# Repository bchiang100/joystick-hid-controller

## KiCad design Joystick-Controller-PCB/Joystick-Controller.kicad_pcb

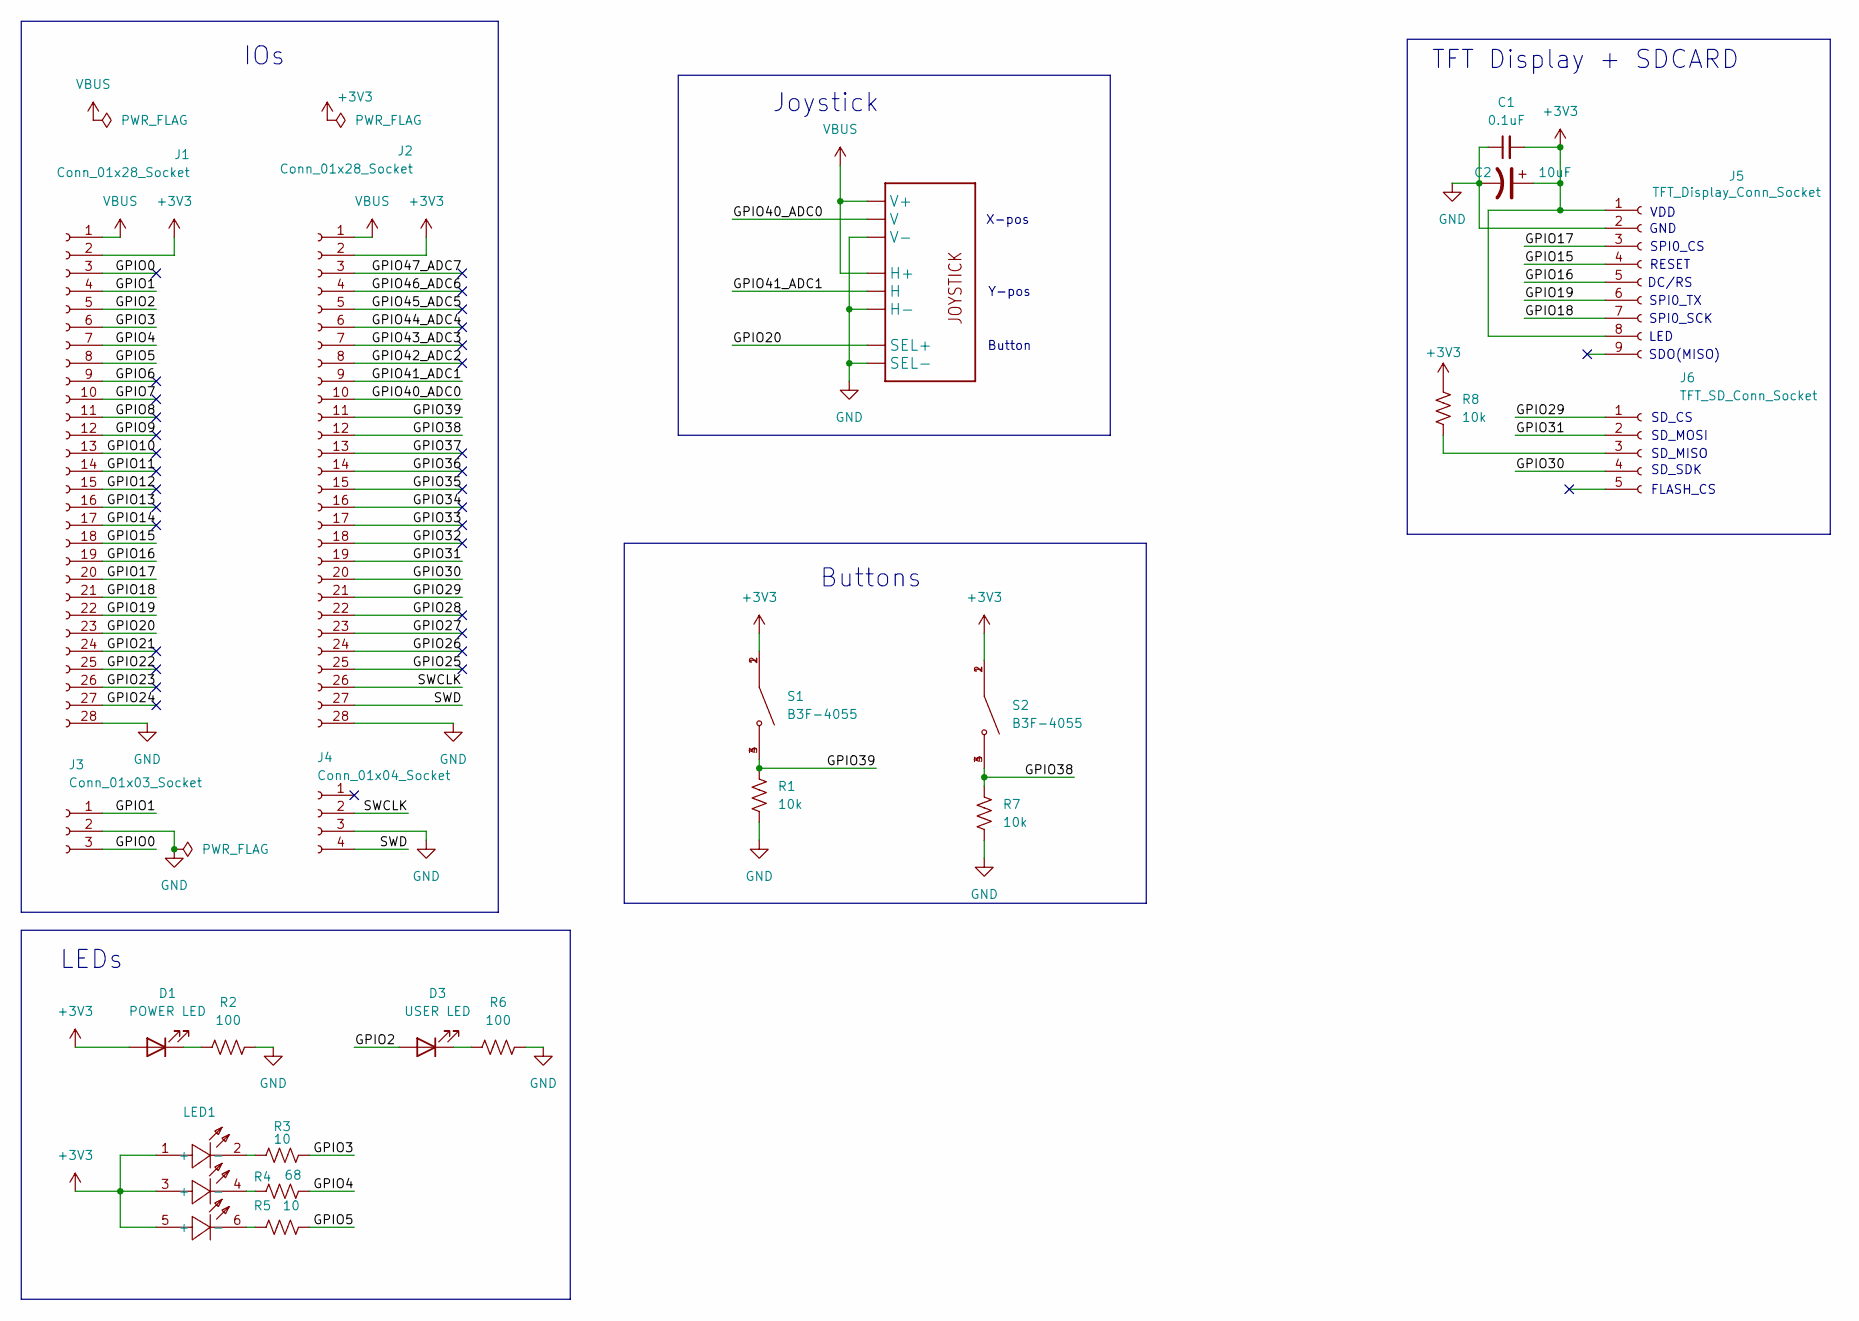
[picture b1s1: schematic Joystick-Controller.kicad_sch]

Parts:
C1: 0.1uF; CP_EIA-2012-12_Kemet-R_HandSolder
C2: 10uF; CP_EIA-2012-12_Kemet-R_HandSolder
D1: POWER LED; D_0805_2012Metric_Pad1.15x1.40mm_HandSolder
D3: USER LED; LED_0603_1608Metric_Pad1.05x0.95mm_HandSolder
J1, J2: Conn_01x28_Socket; PinSocket_1x28_P2.54mm_Vertical
J3: Conn_01x03_Socket; PinSocket_1x03_P2.54mm_Vertical
J4: Conn_01x04_Socket; PinSocket_1x04_P2.54mm_Vertical
J5: TFT_Display_Conn_Socket; PinSocket_1x09_P2.54mm_Vertical
J6: TFT_SD_Conn_Socket; PinSocket_1x05_P2.54mm_Vertical
LED1: LED-SMD_6PIN-L1.60-W1.50-BL-RD; Manufacturer Part E6C1615RGBC3UDA; LCSC Part Name RGB三色
R1, R7, R8: 10k; R_0805_2012Metric_Pad1.20x1.40mm_HandSolder
R2, R6: 100; R_0805_2012Metric_Pad1.20x1.40mm_HandSolder
R3, R5: 10; R_0805_2012Metric_Pad1.20x1.40mm_HandSolder
R4: 68; R_0805_2012Metric_Pad1.20x1.40mm_HandSolder
S1, S2: B3F-4055; SW_B3F-4055; PARTREV A070-E1-08
U1: XDCR_COM-09032

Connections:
+3V3: C1.2, C2.1, D1.2 (A), J1.2, J2.2, J5.1, J5.8, LED1.1 (+), LED1.3 (+), LED1.5 (+), R8.1, S1.1, S1.2, S2.1, S2.2
/GPIO0: J1.3, J3.3
/GPIO1: J1.4, J3.1
/GPIO2: D3.2 (A), J1.5
/GPIO3: J1.6, R3.2
/GPIO4: J1.7, R4.2
/GPIO5: J1.8, R5.2
/GPIO6: J1.9
/GPIO7: J1.10
/GPIO8: J1.11
/GPIO9: J1.12
/GPIO10: J1.13
/GPIO11: J1.14
/GPIO12: J1.15
/GPIO13: J1.16
/GPIO14: J1.17
/GPIO15: J1.18, J5.4
/GPIO16: J1.19, J5.5
/GPIO17: J1.20, J5.3
/GPIO18: J1.21, J5.7
/GPIO19: J1.22, J5.6
/GPIO20: J1.23, U1.B1A (SEL+)
/GPIO21: J1.24
/GPIO22: J1.25
/GPIO23: J1.26
/GPIO24: J1.27
/GPIO25: J2.25
/GPIO26: J2.24
/GPIO27: J2.23
/GPIO28: J2.22
/GPIO29: J2.21, J6.1
/GPIO30: J2.20, J6.4
/GPIO31: J2.19, J6.2
/GPIO32: J2.18
/GPIO33: J2.17
/GPIO34: J2.16
/GPIO35: J2.15
/GPIO36: J2.14
/GPIO37: J2.13
/GPIO38: J2.12, R7.1, S2.3, S2.4
/GPIO39: J2.11, R1.1, S1.3, S1.4
/GPIO40_ADC0: J2.10, U1.V2 (V)
/GPIO41_ADC1: J2.9, U1.H2 (H)
/GPIO42_ADC2: J2.8
/GPIO43_ADC3: J2.7
/GPIO44_ADC4: J2.6
/GPIO45_ADC5: J2.5
/GPIO46_ADC6: J2.4
/GPIO47_ADC7: J2.3
/SWCLK: J2.26, J4.2
/SWD: J2.27, J4.4
GND: C1.1, C2.2, J1.28, J2.28, J3.2, J4.3, J5.2, R1.2, R2.2, R6.2, R7.2, U1.B2A (SEL-), U1.H3 (H-), U1.V3 (V-)
unnamed: D1.1 (K), R2.1
unnamed: D3.1 (K), R6.1
unnamed: J6.3, R8.2
unnamed: LED1.2 (-), R3.1
unnamed: LED1.4 (-), R4.1
unnamed: LED1.6 (-), R5.1
VBUS: J1.1, J2.1, U1.H1 (H+), U1.V1 (V+)

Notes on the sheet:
RESET
TFT Display + SDCARD
SD_CS
FLASH_CS
Joystick
SD_MISO
LED
SD_MOSI
Y-pos
VDD
SPI0_SCK
GND
IOs
X-pos
SPI0_TX
LEDs
SPI0_CS
SD_SDK
DC/RS
Button
Buttons
SDO(MISO)

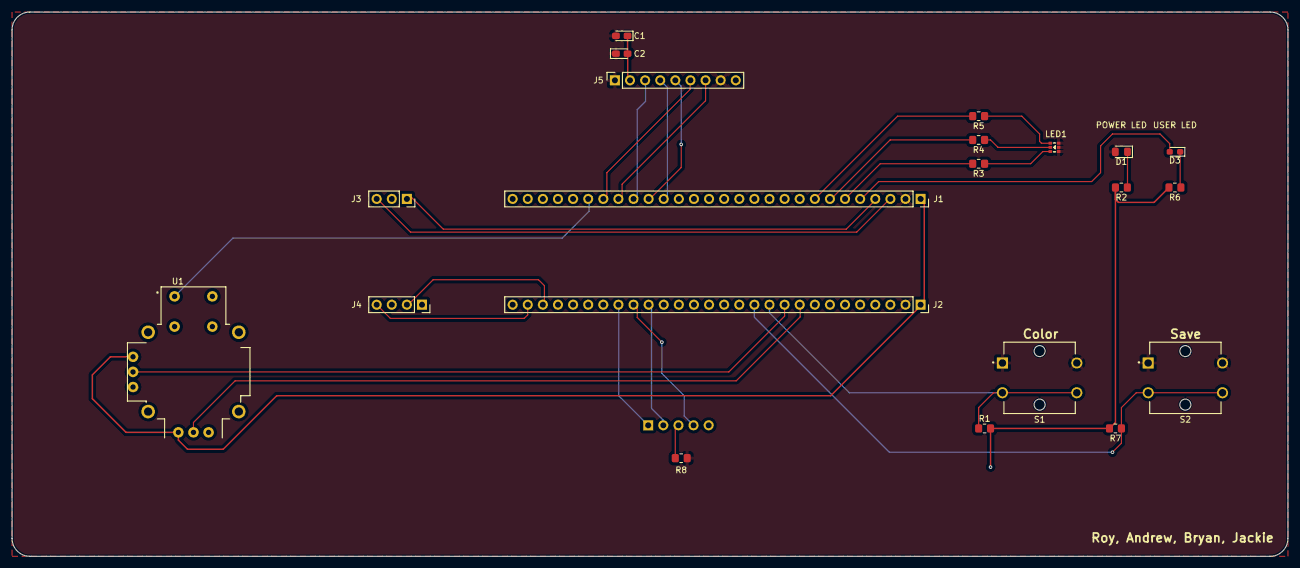
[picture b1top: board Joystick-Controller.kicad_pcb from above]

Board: 2 copper layers, 214.5 x 91.5 mm, 22 parts (1 on the bottom side), 30 nets.

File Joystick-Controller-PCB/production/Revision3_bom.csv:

Designator,Footprint,Quantity,Value,LCSC Part #
C1,CP_EIA-2012-12_Kemet-R_HandSolder,1,0.1uF,
C2,CP_EIA-2012-12_Kemet-R_HandSolder,1,10uF,
D1,0805,1,POWER LED,
D3,0603,1,USER LED,
"J1, J2",PinSocket_1x28_P2.54mm_Vertical,2,Conn_01x28_Socket,
J3,PinSocket_1x03_P2.54mm_Vertical,1,Conn_01x03_Socket,
J4,PinSocket_1x04_P2.54mm_Vertical,1,Conn_01x04_Socket,
J5,PinSocket_1x09_P2.54mm_Vertical,1,TFT_Display_Conn_Socket,
J6,PinSocket_1x05_P2.54mm_Vertical,1,TFT_SD_Conn_Socket,
LED1,LED-SMD_6PIN-L1.60-W1.50-BL-RD,1,~,
"R1, R7, R8",0805,3,10k,
"R2, R6",0805,2,100,
"R3, R5",0805,2,10,
R4,0805,1,68,
"S1, S2",SW_B3F-4055,2,B3F-4055,
U1,XDCR_COM-09032,1,~,

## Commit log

2025-11-06 Uploaded PCB files
2025-11-08 Added TFT schematics
2025-11-09 Mapped GPIO pins to functions. Schematic ready for PCB design
2025-11-10 Placement done
2025-11-11 Iteration 1
2025-11-11 pcb files checked by Niraj
2025-11-12 add working tft lcd display w/o joystick control
2025-11-13 Board Complete
2025-11-13 Updated LED part and resistor values. Added footprint for switch and RGB LED
2025-11-14 add joystick adc functionality
2025-11-14 added color selector and palette
2025-11-15 add ignore DS_Store
2025-11-15 fix gitignore
2025-11-15 Changed buttons to active-low
2025-11-18 add UI and conformed code to PCB design
2025-11-22 addiing usb skeleton
2025-11-22 message
2025-11-22 updated usb code
2025-11-25 Added irq listener to flash user led on button input
2025-11-25 updated rp2350 specefic functions and implemented leds
2025-11-27 started debugging
2025-11-27 working usb mouse
2025-12-02 tested usb code
2025-12-02 updated mouse axis
2025-12-02 working version
